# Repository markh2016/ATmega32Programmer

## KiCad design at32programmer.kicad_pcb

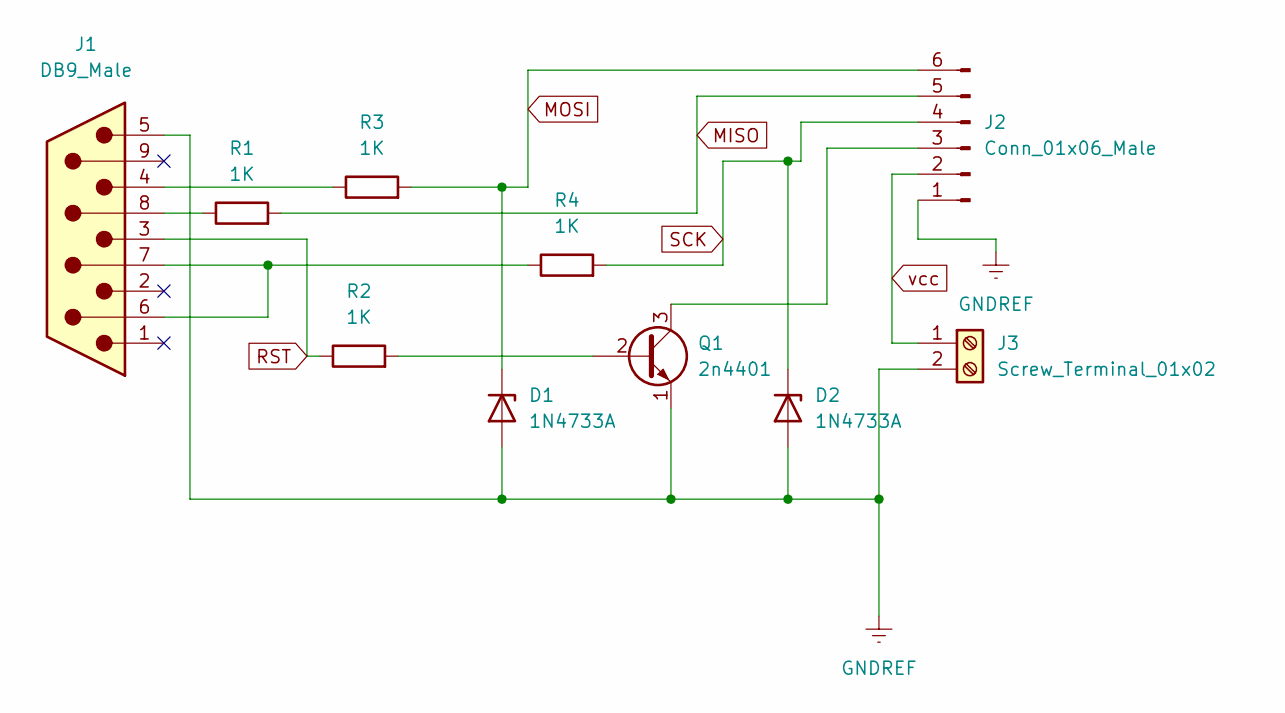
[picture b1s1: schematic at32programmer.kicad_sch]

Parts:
D1, D2: 1N4733A; D_A-405_P10.16mm_Horizontal
J1: DB9_Male; DSUB-9_Male_Horizontal_P2.77x2.84mm_EdgePinOffset4.94mm_Hou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
J2: Conn_01x06_Male; PinHeader_1x06_P2.54mm_Vertical
J3: Screw_Terminal_01x02; TerminalBlock_bornier-2_P5.08mm
Q1: 2n4401; TO-92_Inline
R1: 1K; R_Axial_DIN0207_L6.3mm_D2.5mm_P15.24mm_Horizontal
R2, R3, R4: 1K; R_Axial_DIN0204_L3.6mm_D1.6mm_P7.62mm_Horizontal

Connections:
GNDREF: D1.2 (A), D2.2 (A), J1.5, J2.1, J3.2, Q1.1 (E)
MISO: J2.5, R1.2
MOSI: D1.1 (K), J2.6, R3.2
unnamed: J1.4, R3.1
unnamed: J1.6, J1.7, R4.1
unnamed: J1.8, R1.1
unnamed: J2.3, Q1.3 (C)
unnamed: Q1.2 (B), R2.2
RST: J1.3, R2.1
SCK: D2.1 (K), J2.4, R4.2
vcc: J2.2, J3.1

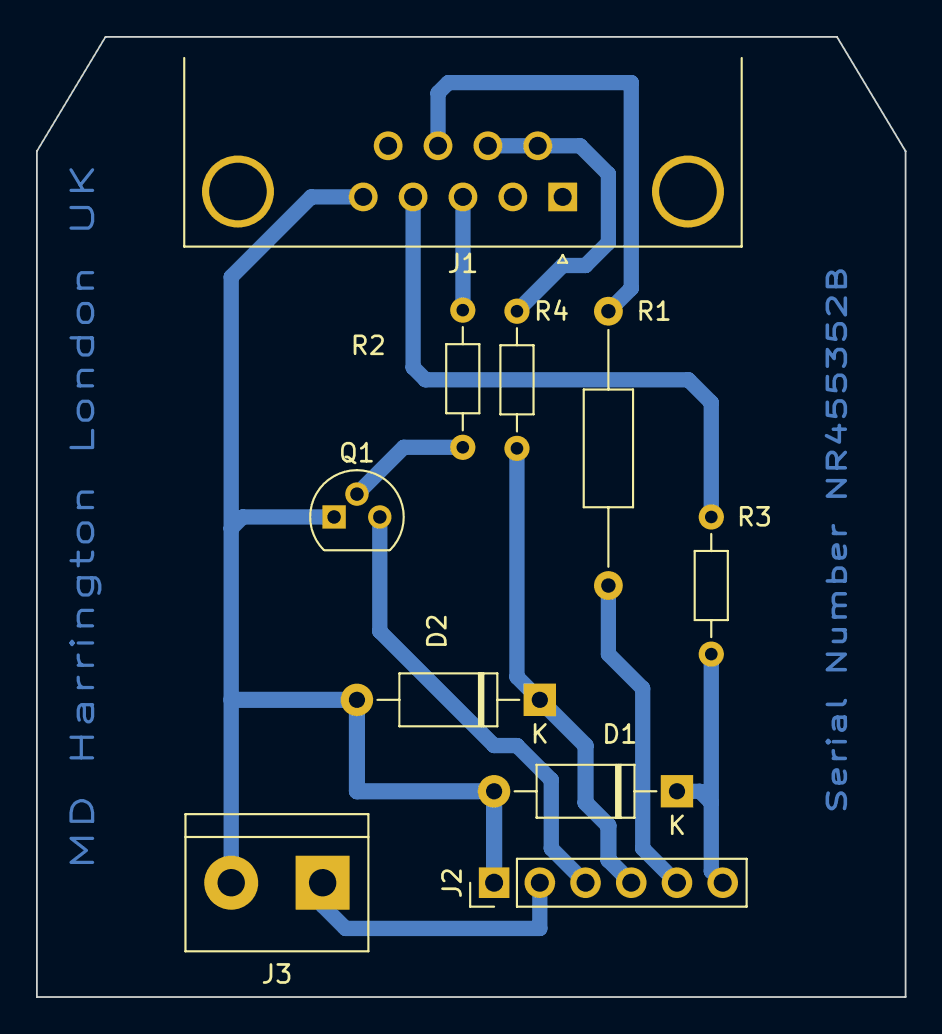
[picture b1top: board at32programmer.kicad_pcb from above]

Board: 2 copper layers, 48.3 x 53.3 mm, 10 parts (0 on the bottom side), 11 nets.
